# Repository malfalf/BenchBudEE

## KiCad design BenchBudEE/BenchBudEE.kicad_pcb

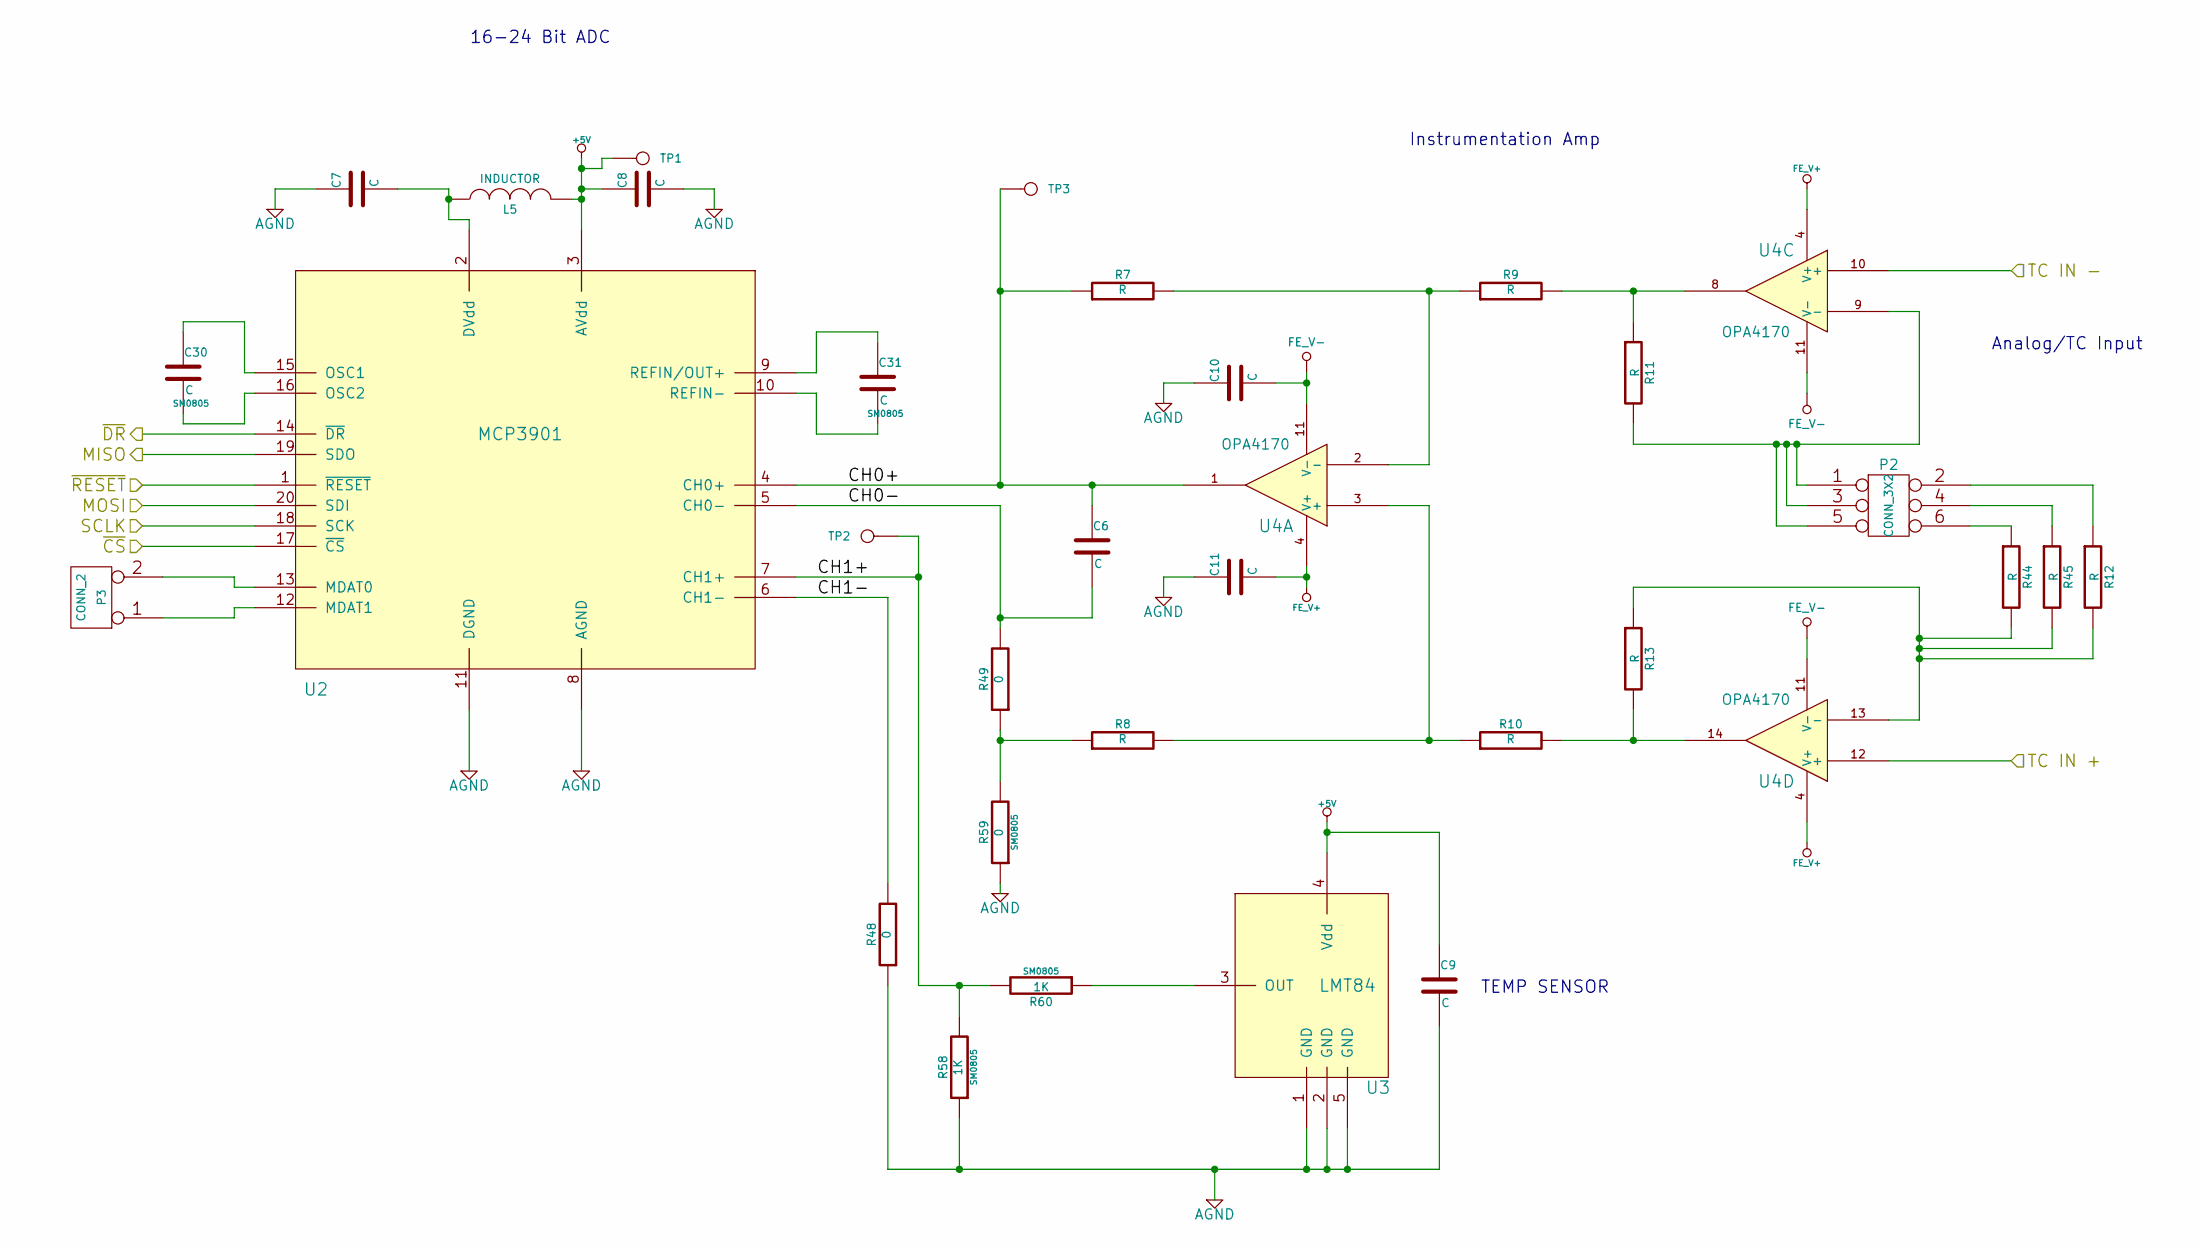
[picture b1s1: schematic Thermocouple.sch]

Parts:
C6, C7, C8, C9, C10, C11: C
C30, C31: C; SM0805
L5: INDUCTOR
P2: CONN_3X2
P3: CONN_2
R7, R8, R9, R10, R11, R12, R13, R44, R45: R
R48, R49: 0
R58, R60: 1K; SM0805
R59: 0; SM0805
TP1: 5V
TP2: CH1+
TP3: CH0+
U2: MCP3901
U3: LMT84
U4: OPA4170

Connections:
+5V: C8.1, C9.1, L5.2, TP1.1, U2.3 (AVdd), U3.4 (Vdd); also elsewhere on the board
/Arduino/MISO: U2.19 (SDO); also elsewhere on the board
/Arduino/MOSI: U2.20 (SDI); also elsewhere on the board
/Arduino/SCLK: U2.18 (SCK); also elsewhere on the board
/Arduino/~ADC_CS: U2.17 (~CS); also elsewhere on the board
/Arduino/~DR: U2.14 (~DR); also elsewhere on the board
/Arduino/~RESET: U2.1 (~RESET); also elsewhere on the board
/Thermocouple/CH0+: C6.1, R7.1, TP3.1, U2.4 (CH0+), U4.1
/Thermocouple/CH0-: C6.2, R49.2, U2.5 (CH0-)
/Thermocouple/CH1+: R58.2, R60.2, TP2.1, U2.7 (CH1+)
/Thermocouple/CH1-: R48.2, U2.6 (CH1-)
/Thermocouple/TC IN +: U4.12 (+); also elsewhere on the board
/Thermocouple/TC IN -: U4.10 (+); also elsewhere on the board
AGND: C7.1, C8.2, C9.2, C10.1, C11.1, R48.1, R58.1, R59.1, U2.8 (AGND), U2.11 (DGND), U3.1 (GND), U3.2 (GND), U3.5 (GND); also elsewhere on the board
FE_V+: C11.2, U4.4 (V+); also elsewhere on the board
FE_V-: C10.2, U4.11 (V-); also elsewhere on the board
unnamed: C7.2, L5.1, U2.2 (DVdd)
unnamed: C30.1, U2.15 (OSC1)
unnamed: R60.1, U3.3 (OUT)
unnamed: C30.2, U2.16 (OSC2)
unnamed: C31.2, U2.10 (REFIN-)
unnamed: P2.4, R45.1
unnamed: P2.6, R44.1
unnamed: R8.2, R10.1, U4.3 (+)
unnamed: R7.2, R9.1, U4.2 (-)
unnamed: P2.2, R12.1
unnamed: R9.2, R11.1, U4.8
unnamed: R10.2, R13.2, U4.14
unnamed: P3.2 (PM), U2.13 (MDAT0)
unnamed: P3.1, U2.12 (MDAT1)
unnamed: C31.1, U2.9 (REFIN/OUT+)
unnamed: R8.1, R49.1, R59.2
unnamed: R12.2, R13.1, R44.2, R45.2, U4.13 (-)
unnamed: P2.1, P2.3, P2.5, R11.2, U4.9 (-)

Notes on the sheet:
Analog/TC Input
Instrumentation Amp
16-24 Bit ADC
TEMP SENSOR

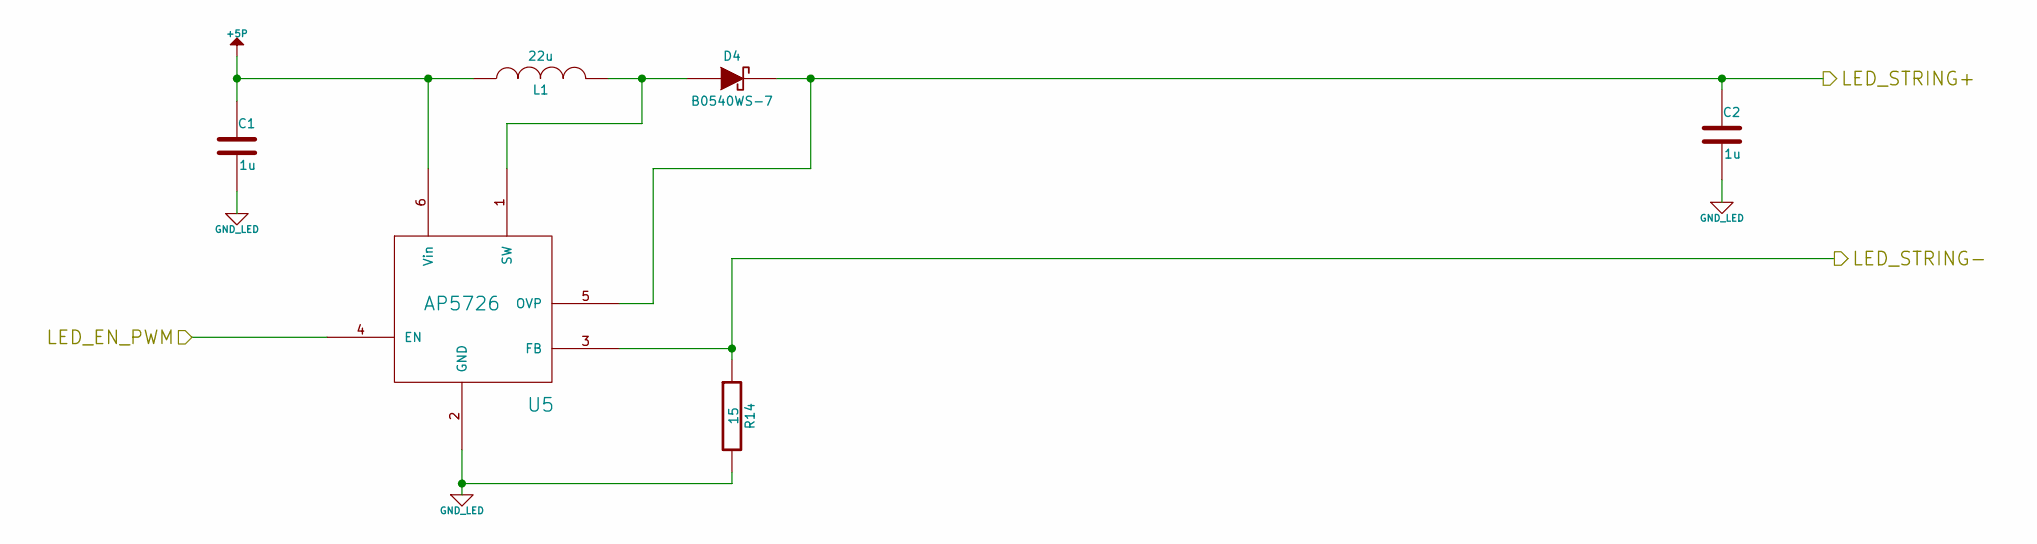
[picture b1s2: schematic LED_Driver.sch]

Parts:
C1, C2: 1u
D4: B0540WS-7
L1: 22u; MFG Part Number NR4012T220M
R14: 15
U5: AP5726

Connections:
+5P: C1.1, L1.1, U5.6 (Vin); also elsewhere on the board
/Arduino/LED_EN_PWM: U5.4 (EN); also elsewhere on the board
/LED_Driver/LED_STRING+: C2.1, D4.2 (K), U5.5 (OVP); also elsewhere on the board
/LED_Driver/LED_STRING-: R14.1, U5.3 (FB); also elsewhere on the board
GND_LED: C1.2, C2.2, R14.2, U5.2 (GND); also elsewhere on the board
unnamed: D4.1 (A), L1.2, U5.1 (SW)

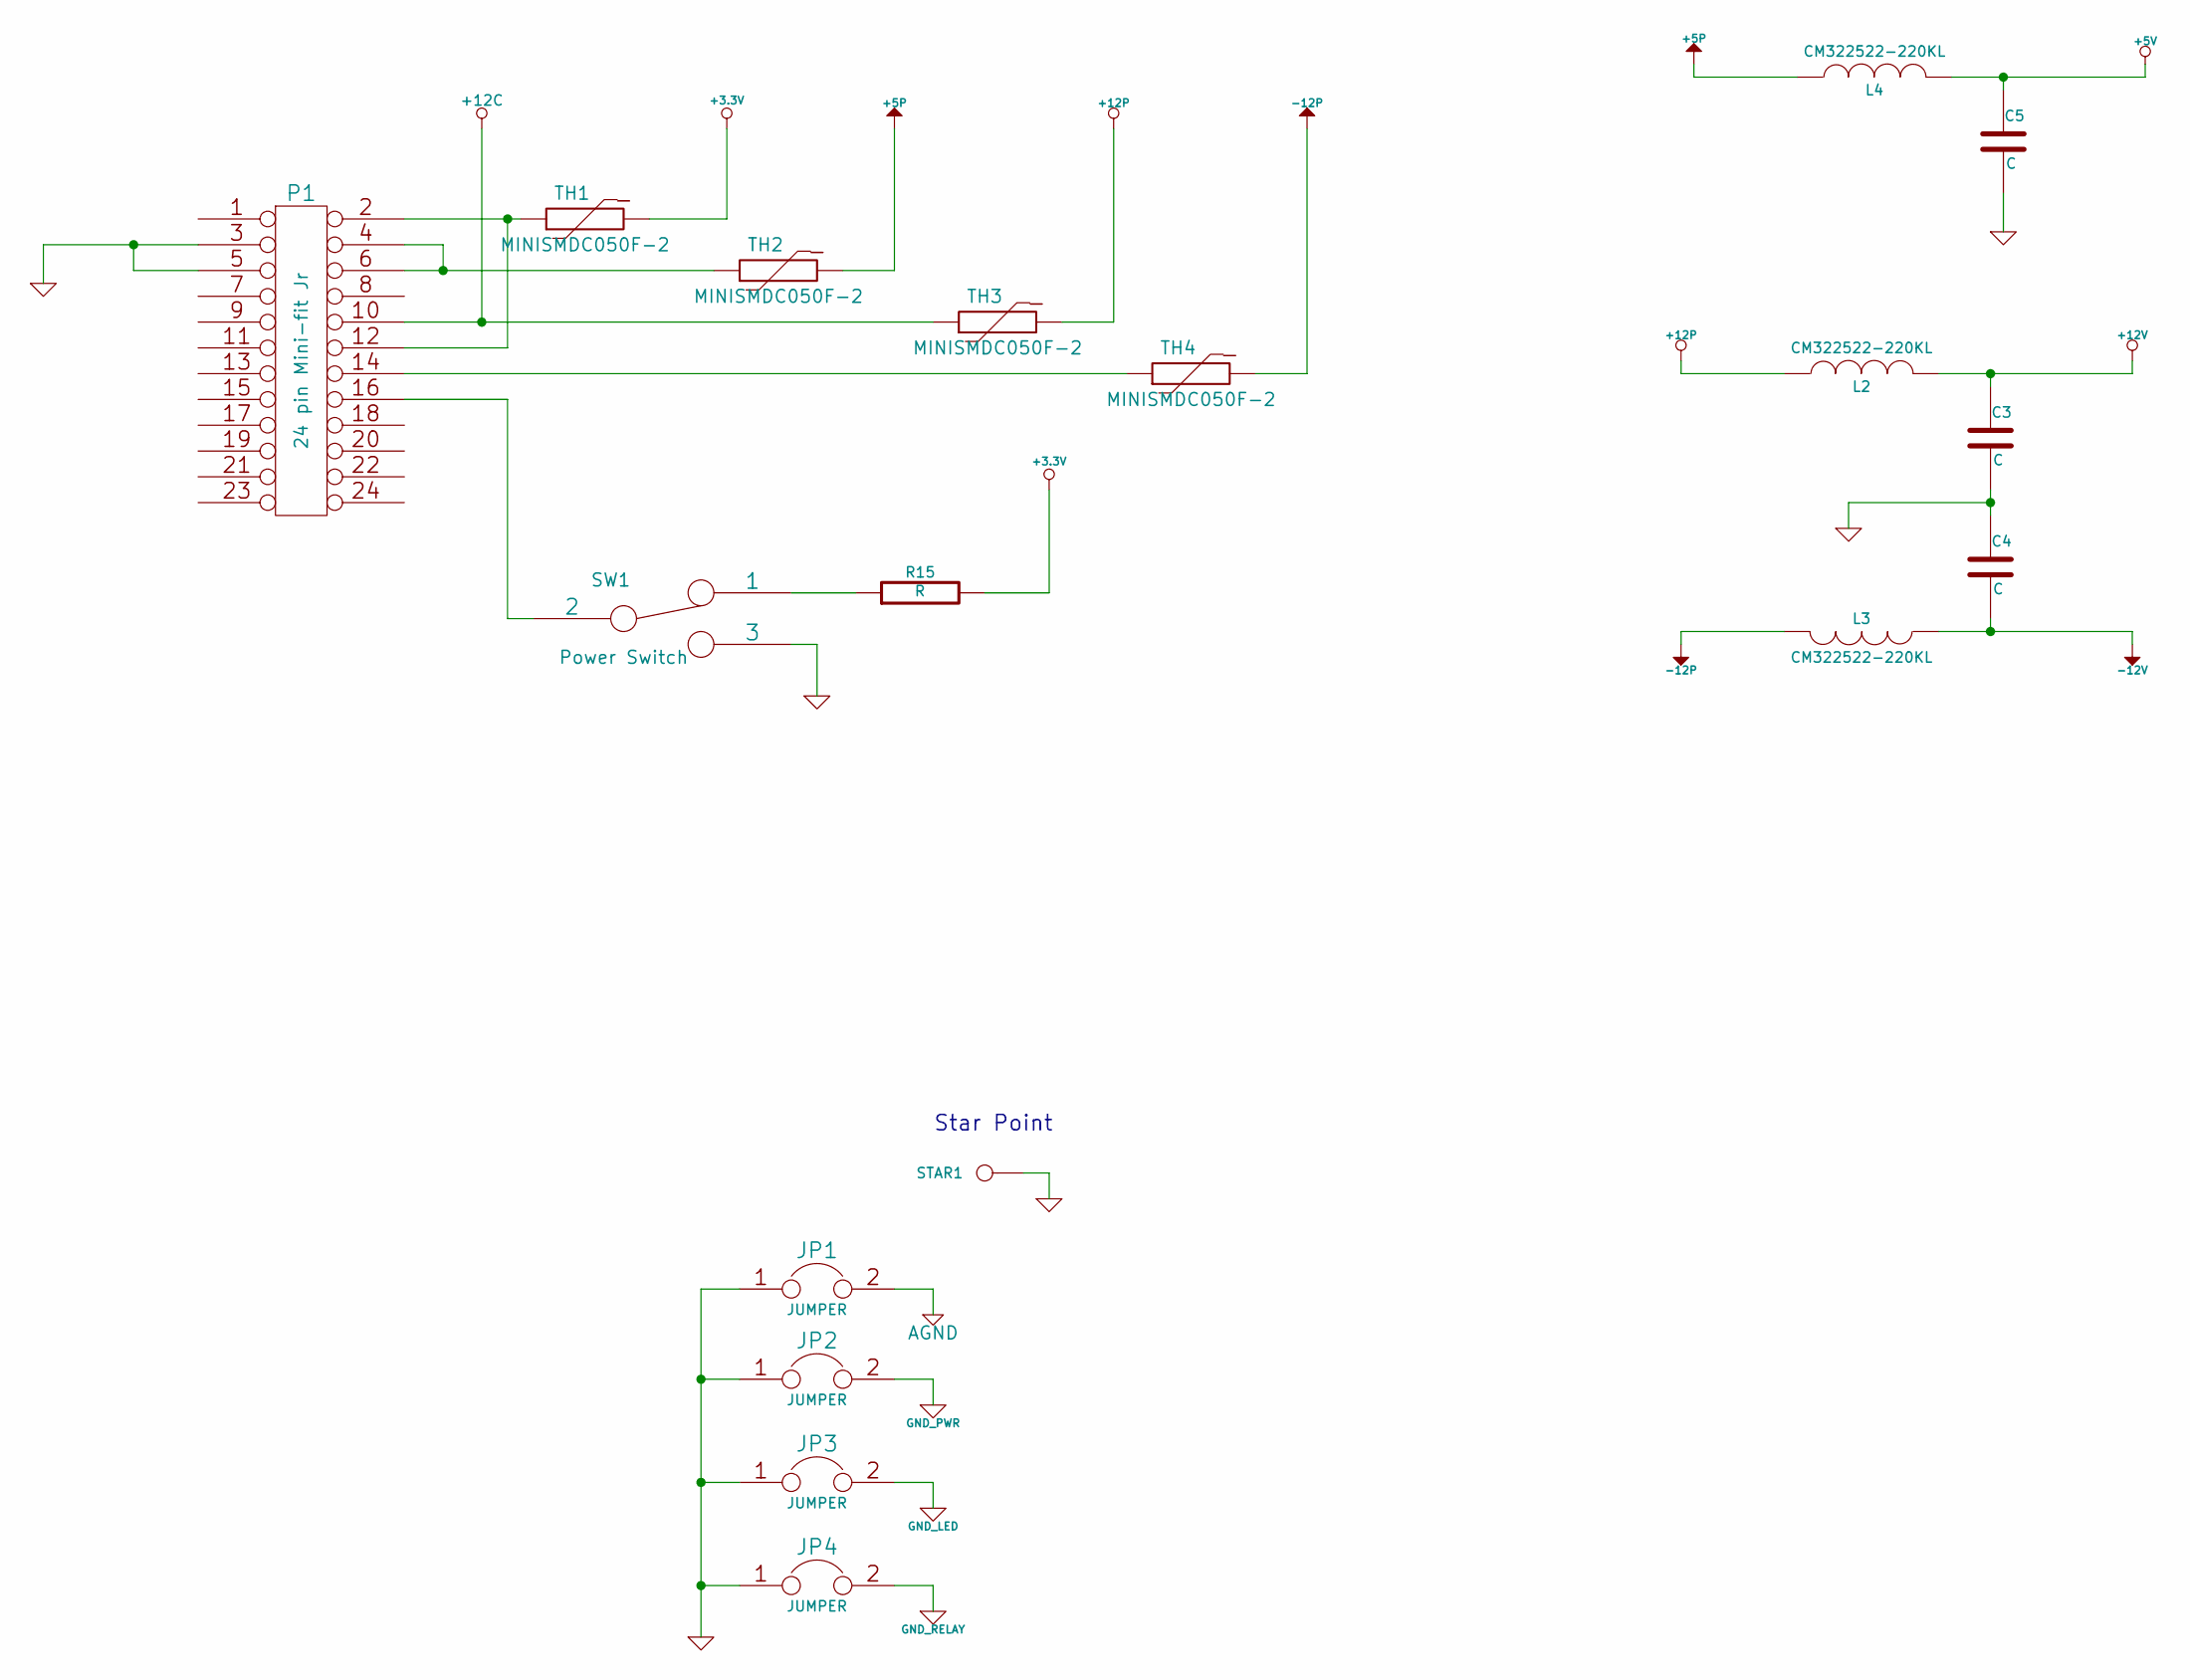
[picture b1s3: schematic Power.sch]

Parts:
C3, C4, C5: C
JP1, JP2, JP3, JP4: JUMPER
L2, L3, L4: CM322522-220KL; MFG Part Number CM322522-220KL
P1: 24 pin Mini-fit Jr; MFG Part Number 39-30-1240
R15: R
STAR1: CONN_1
SW1: Power Switch; MFG Part Number OS102011MA1QN1
TH1, TH2, TH3, TH4: MINISMDC050F-2; MFG Part Number MINISMDC050F-2

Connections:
+3.3V: R15.2, TH1.2; also elsewhere on the board
+5P: L4.1, TH2.2; also elsewhere on the board
+5V: C5.1, L4.2; also elsewhere on the board
+12C: P1.10, TH3.1; also elsewhere on the board
+12P: L2.1, TH3.2; also elsewhere on the board
+12V: C3.1, L2.2; also elsewhere on the board
-12P: L3.2, TH4.2
-12V: C4.2, L3.1; also elsewhere on the board
AGND: JP1.2; also elsewhere on the board
GND: C3.2, C4.1, C5.2, JP1.1, JP2.1, JP3.1, JP4.1, P1.3, P1.5, STAR1.1, SW1.3; also elsewhere on the board
GND_LED: JP3.2; also elsewhere on the board
GND_PWR: JP2.2; also elsewhere on the board
GND_RELAY: JP4.2; also elsewhere on the board
unnamed: P1.14, TH4.1
unnamed: P1.16, SW1.2
unnamed: P1.4, P1.6, TH2.1
unnamed: R15.1, SW1.1
unnamed: P1.2, P1.12, TH1.1

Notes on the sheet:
Star Point

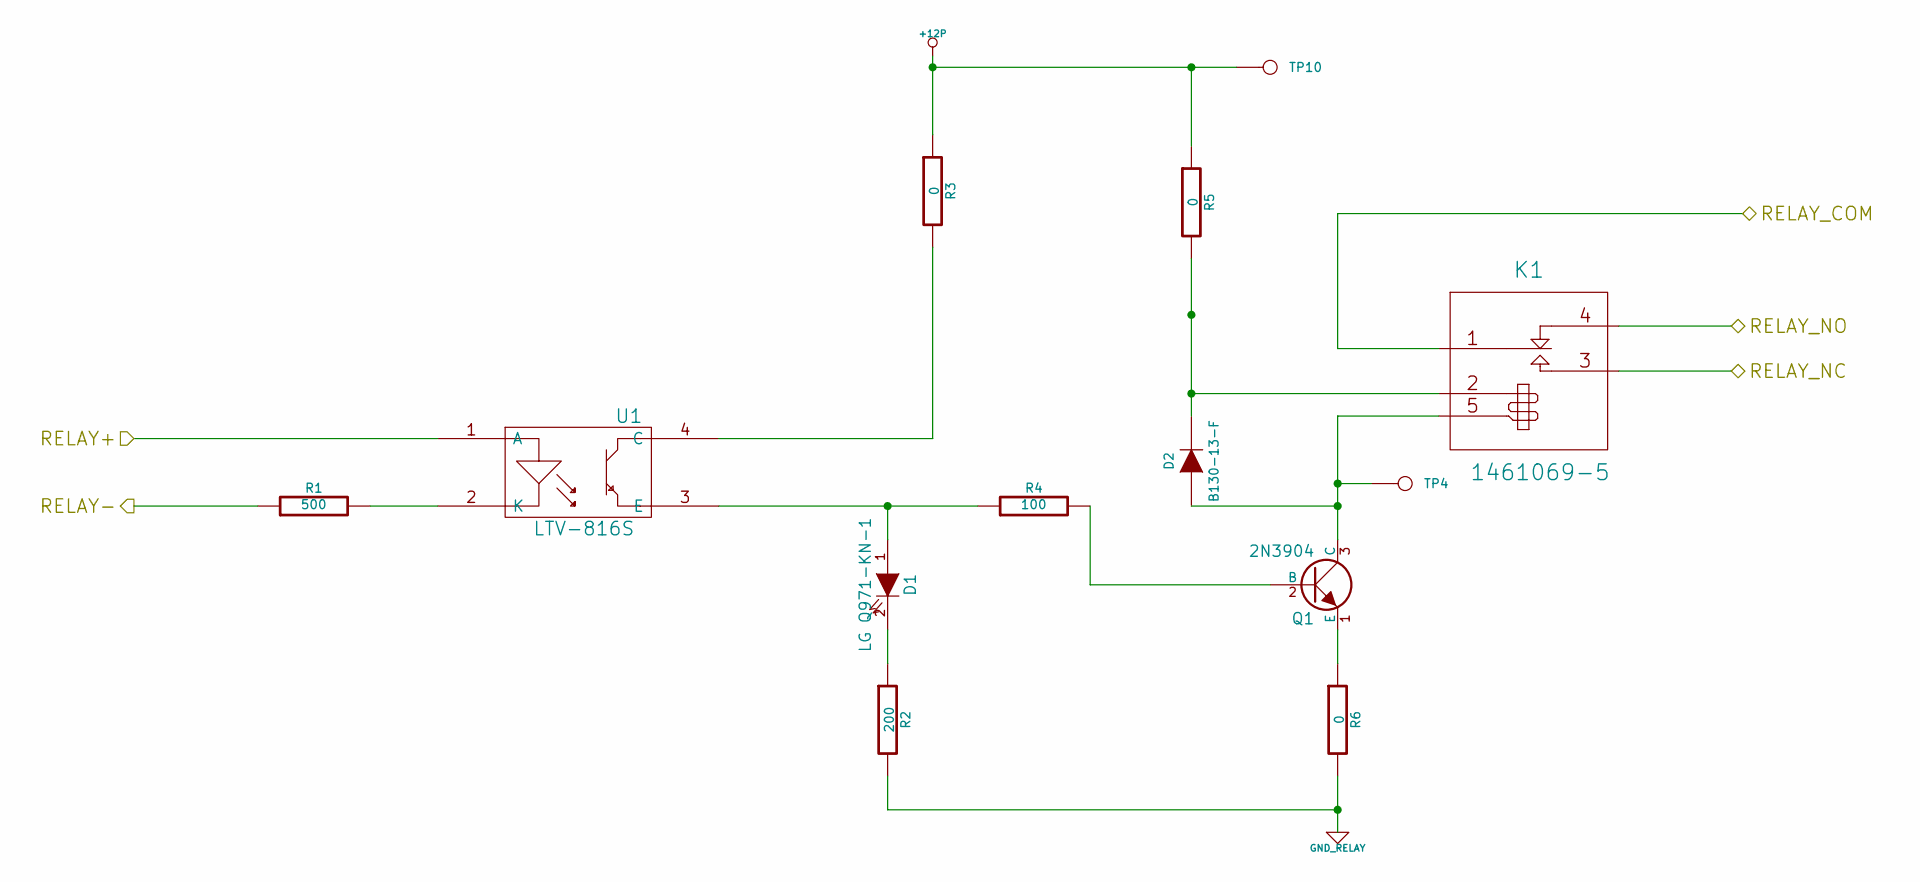
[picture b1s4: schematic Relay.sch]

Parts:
D1: LG Q971-KN-1
D2: B130-13-F
K1: 1461069-5
Q1: 2N3904; MFG Part Number MMBT3904-7-F
R1: 500
R2: 200
R3, R5, R6: 0
R4: 100
TP4: RELAY_LOW
TP10: 12P
U1: LTV-816S; MFG Part Number LTV-816S

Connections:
+12P: R3.1, R5.1, TP10.1; also elsewhere on the board
/Arduino/RELAY+: U1.1 (A); also elsewhere on the board
/Arduino/RELAY-: R1.1; also elsewhere on the board
/Relay/RELAY_COM: K1.1 (COM); also elsewhere on the board
/Relay/RELAY_NC: K1.3 (NO); also elsewhere on the board
/Relay/RELAY_NO: K1.4 (NC); also elsewhere on the board
GND_RELAY: R2.2, R6.2; also elsewhere on the board
unnamed: D1.2 (K), R2.1
unnamed: Q1.1 (E), R6.1
unnamed: D1.1 (A), R4.1, U1.3 (E)
unnamed: Q1.2 (B), R4.2
unnamed: R1.2, U1.2 (K)
unnamed: D2.2 (K), K1.2 (COIL+), R5.2
unnamed: R3.2, U1.4 (C)
unnamed: D2.1 (A), K1.5 (COIL-), Q1.3 (C), TP4.1

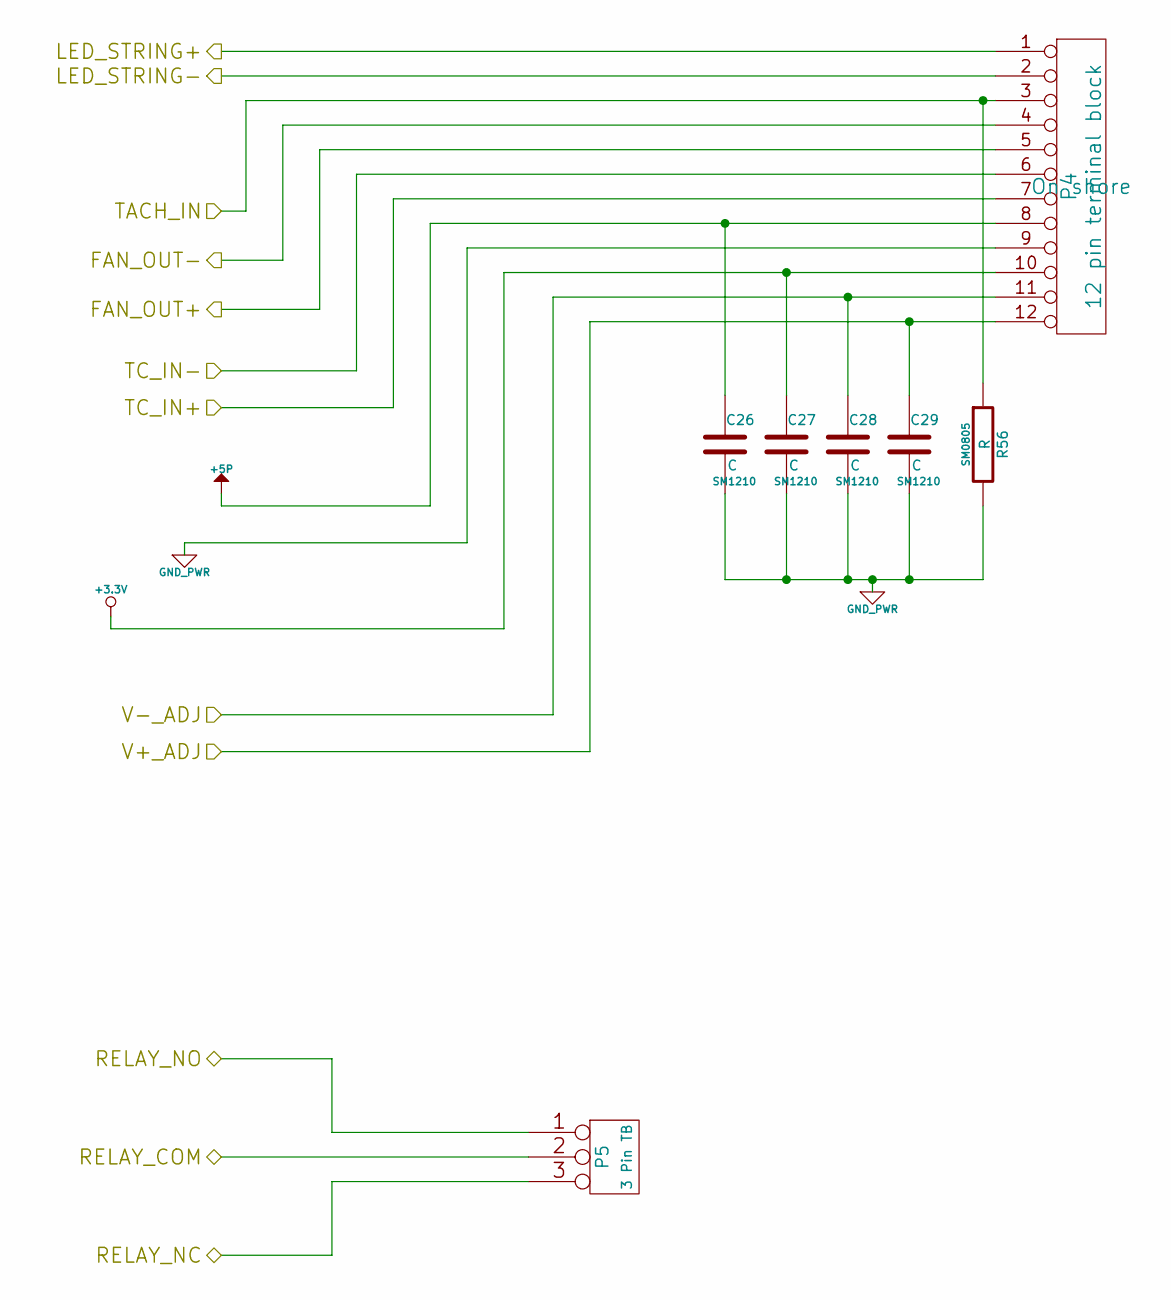
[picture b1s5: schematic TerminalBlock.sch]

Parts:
C26, C27, C28, C29: C; SM1210
P4: 12 pin terminal block; MFG Part Number OSTTE120104
P5: 3 Pin TB; MFG Part Number 1935174
R56: R; SM0805

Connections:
+3.3V: C27.1, P4.10; also elsewhere on the board
+5P: C26.1, P4.8; also elsewhere on the board
/Fan/FAN_OUT+: P4.5; also elsewhere on the board
/Fan/FAN_OUT-: P4.4; also elsewhere on the board
/Fan/TACH_IN: P4.3, R56.1; also elsewhere on the board
/LED_Driver/LED_STRING+: P4.1; also elsewhere on the board
/LED_Driver/LED_STRING-: P4.2; also elsewhere on the board
/PowerAdjustmentMonitor/V+_ADJ: C29.1, P4.12; also elsewhere on the board
/PowerAdjustmentMonitor/V-_ADJ: C28.1, P4.11; also elsewhere on the board
/Relay/RELAY_COM: P5.2 (PM); also elsewhere on the board
/Relay/RELAY_NC: P5.3; also elsewhere on the board
/Relay/RELAY_NO: P5.1; also elsewhere on the board
/Thermocouple/TC IN +: P4.7; also elsewhere on the board
/Thermocouple/TC IN -: P4.6; also elsewhere on the board
GND_PWR: C26.2, C27.2, C28.2, C29.2, P4.9, R56.2; also elsewhere on the board

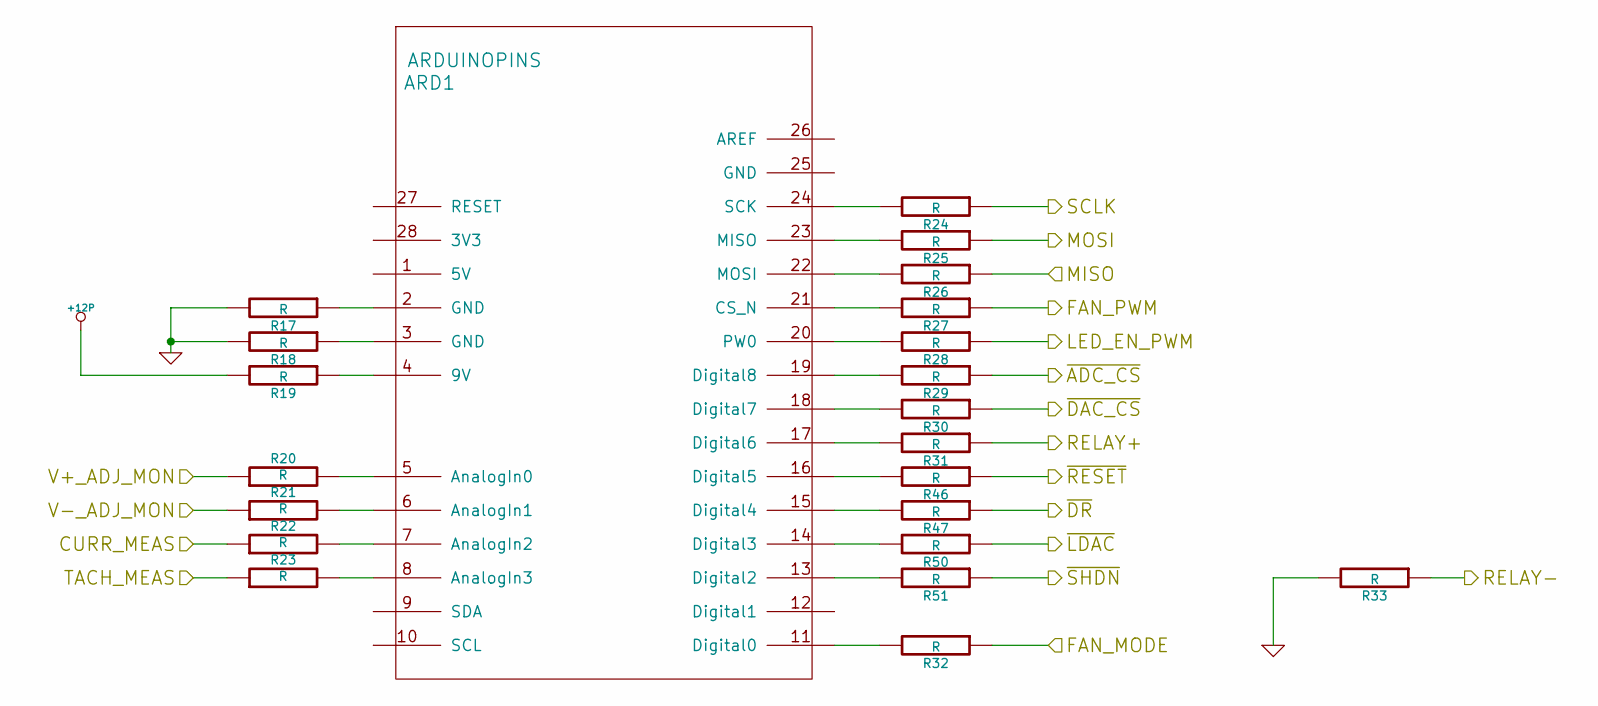
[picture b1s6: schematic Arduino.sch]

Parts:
ARD1: ARDUINOPINS
R17, R18, R19, R20, R21, R22, R23, R24, R25, R26, R27, R28, R29, R30, R31, R32, R33, R46, R47, R50, R51: R

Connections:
+12P: R19.2; also elsewhere on the board
/Arduino/CURR_MEAS: R22.1; also elsewhere on the board
/Arduino/FAN_MODE: R32.1; also elsewhere on the board
/Arduino/FAN_PWM: R27.1; also elsewhere on the board
/Arduino/LED_EN_PWM: R28.1; also elsewhere on the board
/Arduino/MISO: R26.1; also elsewhere on the board
/Arduino/MOSI: R25.1; also elsewhere on the board
/Arduino/RELAY+: R31.1; also elsewhere on the board
/Arduino/RELAY-: R33.1; also elsewhere on the board
/Arduino/SCLK: R24.1; also elsewhere on the board
/Arduino/V+_ADJ_MON: R20.1; also elsewhere on the board
/Arduino/V-_ADJ_MON: R21.1; also elsewhere on the board
/Arduino/~ADC_CS: R29.1; also elsewhere on the board
/Arduino/~DR: R47.1; also elsewhere on the board
/Arduino/~LDAC: R50.1; also elsewhere on the board
/Arduino/~RESET: R46.1; also elsewhere on the board
/Fan/CS_N: R30.1; also elsewhere on the board
/Fan/TACH_IN: R23.1; also elsewhere on the board
/Fan/~SDHN: R51.1; also elsewhere on the board
GND: R17.2, R18.2, R33.2; also elsewhere on the board
unnamed: ARD1.11 (Digital0), R32.2
unnamed: ARD1.15 (Digital4), R47.2
unnamed: ARD1.17 (Digital6), R31.2
unnamed: ARD1.4 (9V), R19.1
unnamed: ARD1.16 (Digital5), R46.2
unnamed: ARD1.14 (Digital3), R50.2
unnamed: ARD1.13 (Digital2), R51.2
unnamed: ARD1.2 (GND), R17.1
unnamed: ARD1.3 (GND), R18.1
unnamed: ARD1.7 (AnalogIn2), R22.2
unnamed: ARD1.8 (AnalogIn3), R23.2
unnamed: ARD1.6 (AnalogIn1), R21.2
unnamed: ARD1.5 (AnalogIn0), R20.2
unnamed: ARD1.21 (CS_N), R27.2
unnamed: ARD1.20 (PW0), R28.2
unnamed: ARD1.19 (Digital8), R29.2
unnamed: ARD1.18 (Digital7), R30.2
unnamed: ARD1.22 (MOSI), R26.2
unnamed: ARD1.23 (MISO), R25.2
unnamed: ARD1.24 (SCK), R24.2

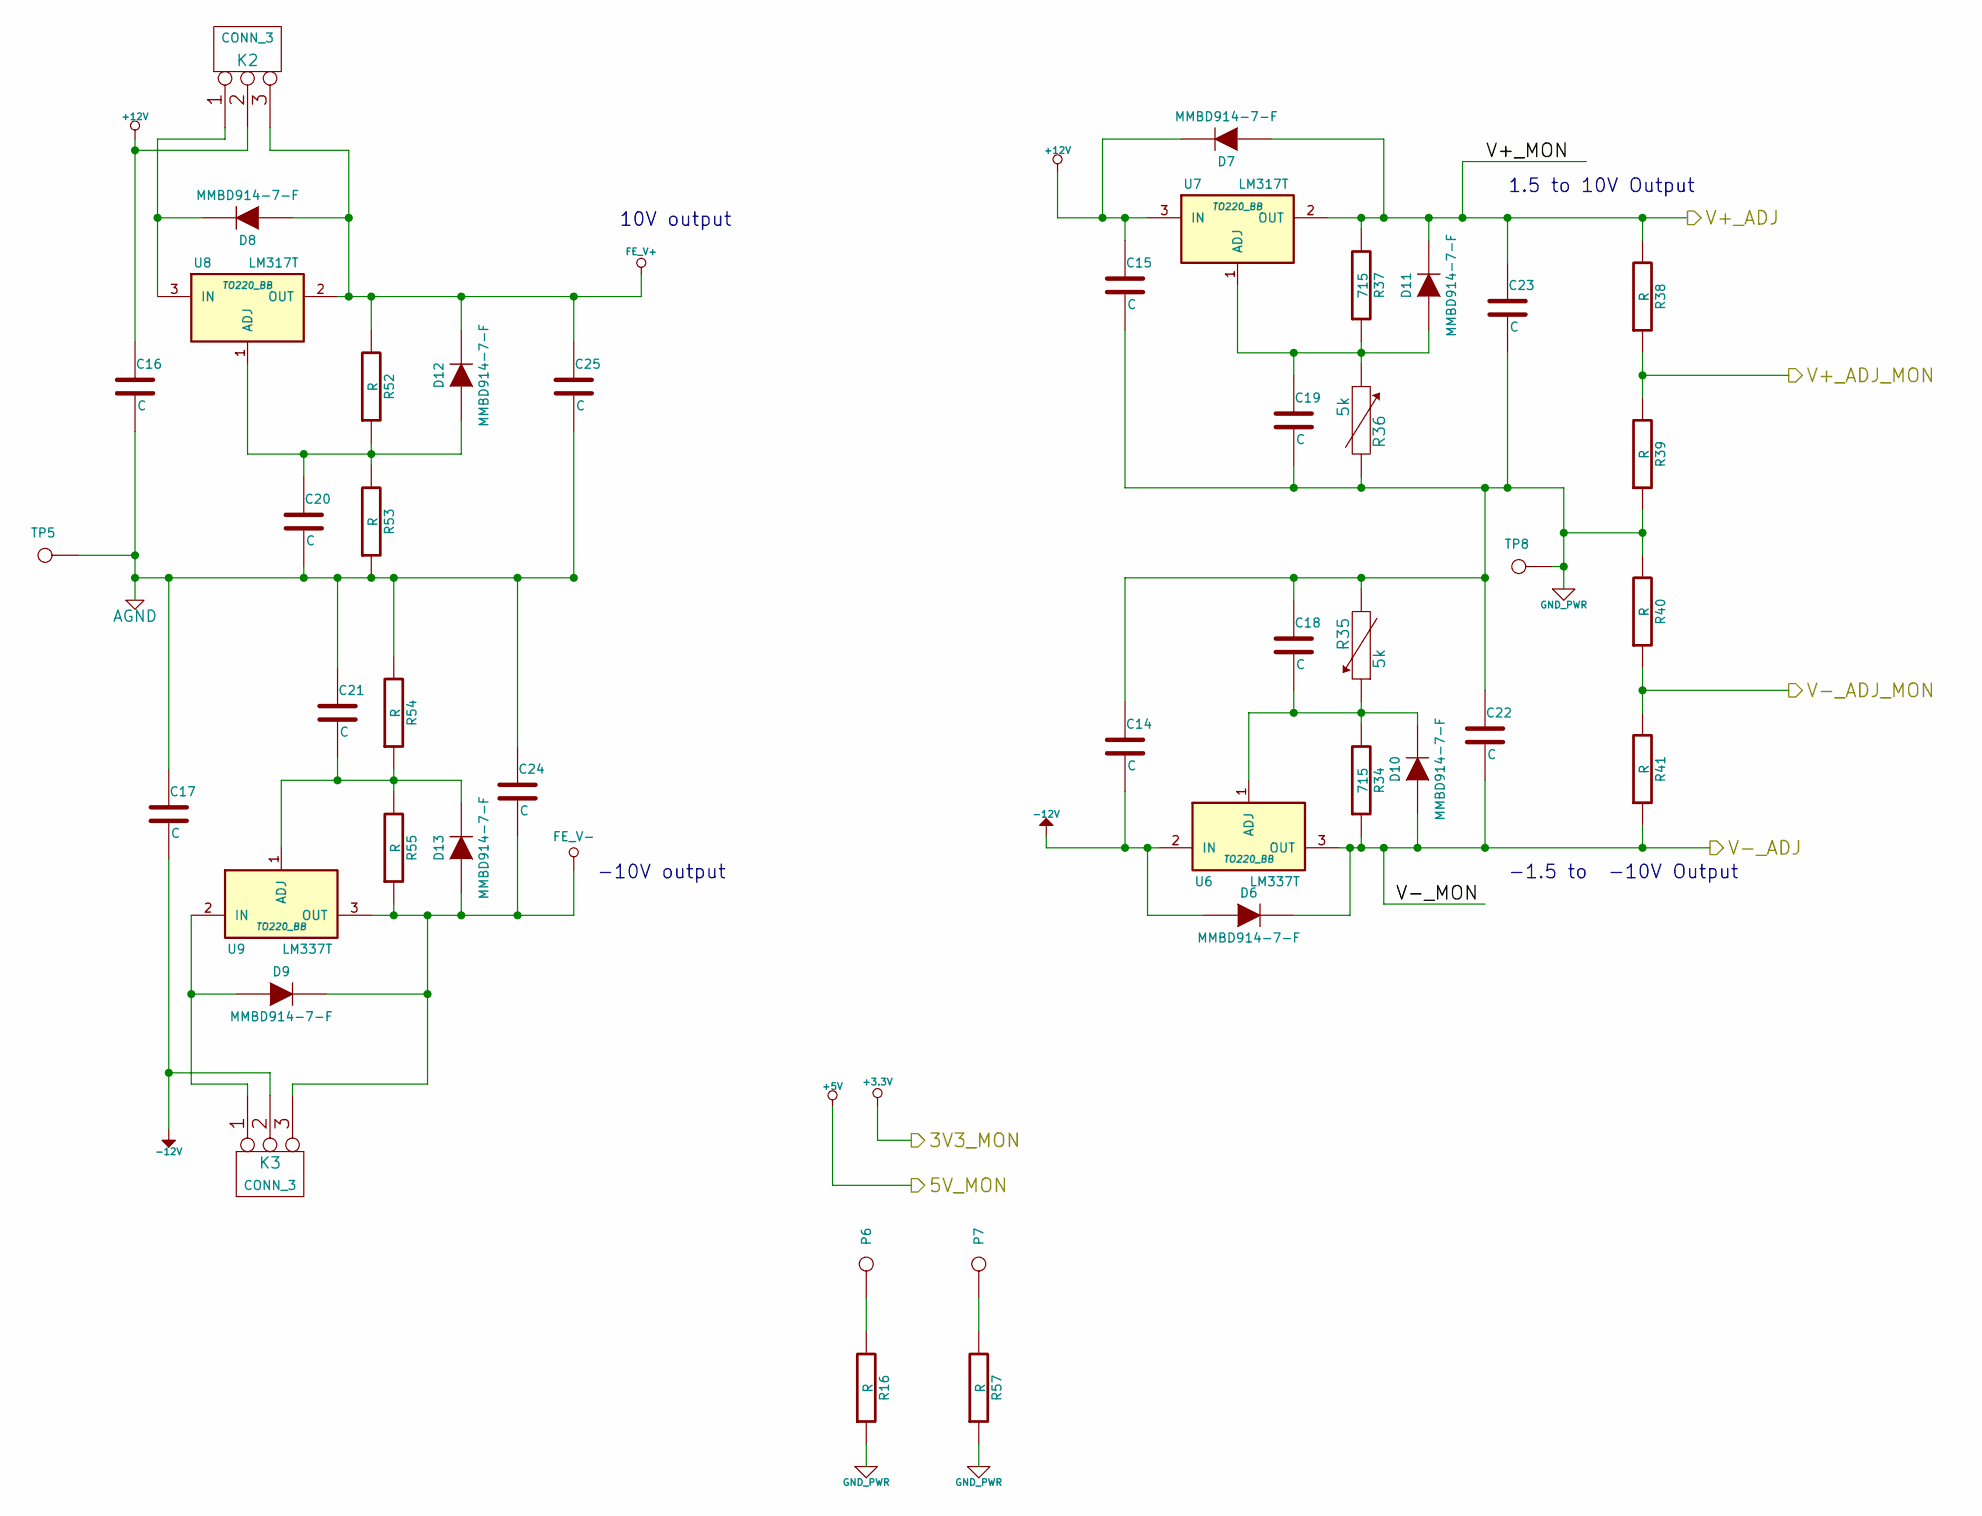
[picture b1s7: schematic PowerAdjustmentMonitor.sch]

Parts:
C14, C15, C16, C17, C18, C19, C20, C21, C22, C23, C24, C25: C
D6, D7, D8, D9, D10, D11, D12, D13: MMBD914-7-F
K2, K3: CONN_3
P6, P7: CONN_1
R16, R38, R39, R40, R41, R52, R53, R54, R55, R57: R
R34, R37: 715
R35, R36: 5k
TP5: AGND
TP8: GND_PWR
U6, U9: LM337T; TO220_BB
U7, U8: LM317T; TO220_BB

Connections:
+12V: C15.1, C16.1, D7.2 (K), K2.2 (PM), U7.3 (IN); also elsewhere on the board
-12V: C14.2, C17.2, D6.1 (A), K3.2 (PM), U6.2 (IN); also elsewhere on the board
/Arduino/V+_ADJ_MON: R38.1, R39.2; also elsewhere on the board
/Arduino/V-_ADJ_MON: R40.1, R41.2; also elsewhere on the board
/PowerAdjustmentMonitor/V+_ADJ: C23.1, D7.1 (A), D11.2 (K), R37.2, R38.2, U7.2 (OUT); also elsewhere on the board
/PowerAdjustmentMonitor/V-_ADJ: C22.2, D6.2 (K), D10.1 (A), R34.1, R41.1, U6.3 (OUT); also elsewhere on the board
AGND: C16.2, C17.1, C20.2, C21.1, C24.1, C25.2, R53.1, R54.2, TP5.1; also elsewhere on the board
FE_V+: C25.1, D8.1 (A), D12.2 (K), K2.3, R52.2, U8.2 (OUT); also elsewhere on the board
FE_V-: C24.2, D9.2 (K), D13.1 (A), K3.3, R55.1, U9.3 (OUT); also elsewhere on the board
GND_PWR: C14.1, C15.2, C18.1, C19.2, C22.1, C23.2, R16.1, R35.2, R36.2, R39.1, R40.2, R57.1, TP8.1; also elsewhere on the board
unnamed: D8.2 (K), K2.1, U8.3 (IN)
unnamed: P7.1, R57.2
unnamed: P6.1, R16.2
unnamed: D9.1 (A), K3.1, U9.2 (IN)
unnamed: C19.1, D11.1 (A), R36.1, R37.1, U7.1 (ADJ)
unnamed: C20.1, D12.1 (A), R52.1, R53.2, U8.1 (ADJ)
unnamed: C21.2, D13.2 (K), R54.1, R55.2, U9.1 (ADJ)
unnamed: C18.2, D10.2 (K), R34.2, R35.1, U6.1 (ADJ)

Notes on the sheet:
10V output
1.5 to 10V Output
-10V output
-1.5 to -10V Output
